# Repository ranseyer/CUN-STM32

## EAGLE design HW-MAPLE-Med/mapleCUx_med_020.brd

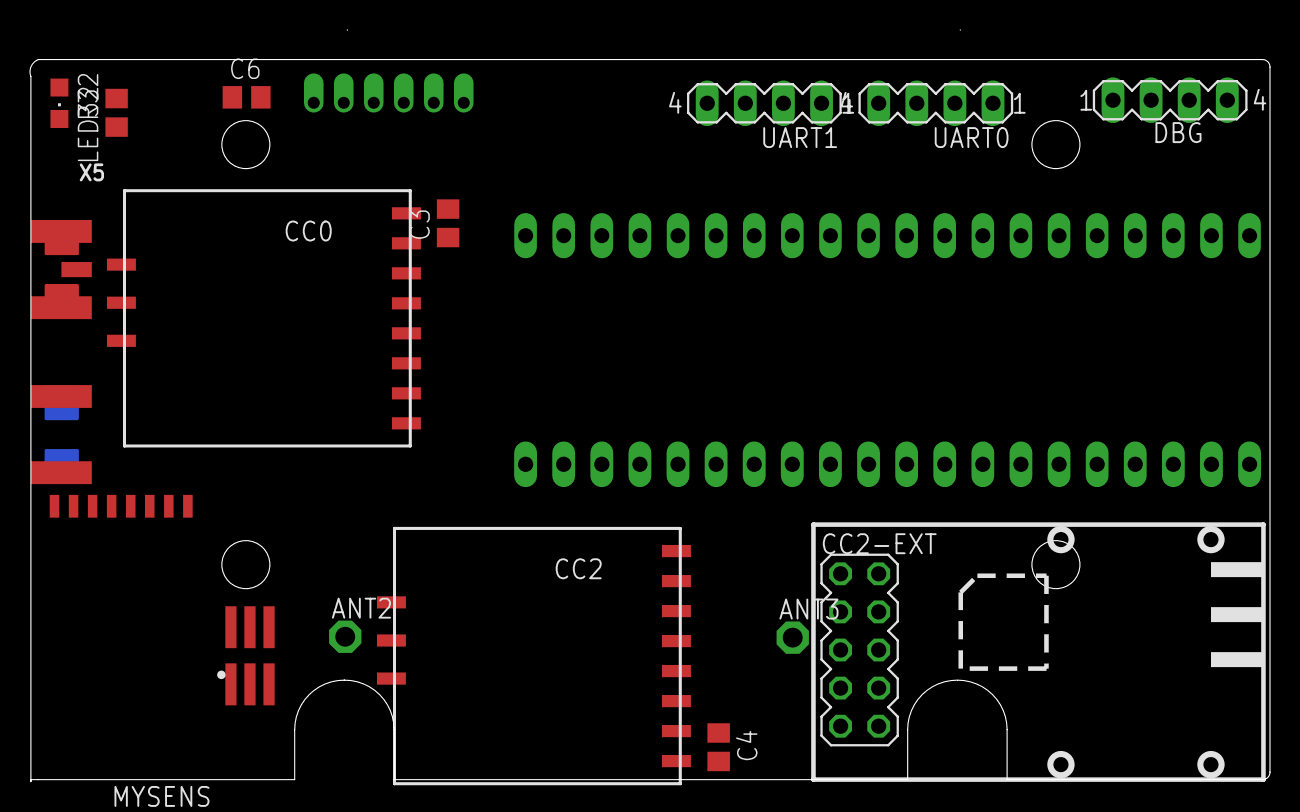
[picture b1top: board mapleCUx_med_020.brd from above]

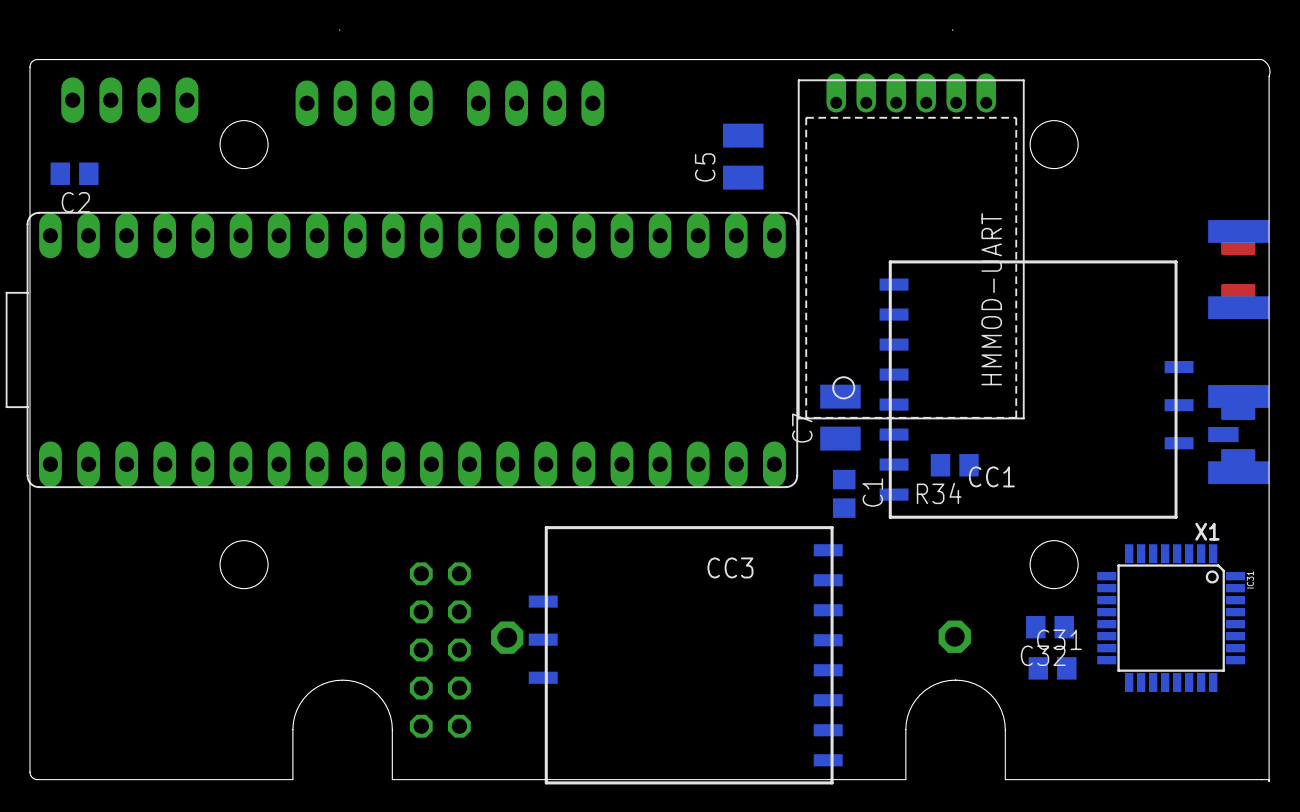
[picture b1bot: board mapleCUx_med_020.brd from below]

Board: 2 copper layers, 82.7 x 50.1 mm, 29 parts (13 on the bottom side), 36 nets, no tracks yet.

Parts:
ANT2, ANT3: TPPAD1-13; P1-13
C1, C2, C3, C4, C6: 22pF; C0805
C5: 10uF; C1210
C7: 4,7uF; C1210
C31, C32: 100n; C0805
CC0: CC1101; CC1101_MODULE1_SMD
CC1, CC2, CC3: CC1101_MODULE1SMD; CC1101_MODULE1_SMD
CC2-EXT: CC1101_MODULE3_DIL
DBG: MA04-1
HMMOD-UART: HM-MOD-UARTDIL; HM-MOD-UART-DIL
IC31: ATMEGA168-TQFP; TQFP32-08
LED32: CHIPLED_0805
MYSENS: NRF24L01+SMD
R32: 1k; R0805
R34: R0805
U$4: MAPLEMINI; 20-DIP
UART0, UART1: MA04-1
X1, X5: SMA_EDGELAUNCH_UFL
X31: M03X2; 2X03-1.27MM_SMD

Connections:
CC_CS0: CC0.CSN, U$4.29
CC_CS1: CC1.CSN, U$4.35
CC_CS2: CC2.CSN, CC2-EXT.CSN, U$4.4
CC_CS3: CC3.CSN, U$4.25
CC_IN_0: CC0.GDO2, U$4.33
CC_IN_1: CC1.GDO2, U$4.7
CC_IN_2: CC2.GDO2, CC2-EXT.GDO2, U$4.5
CC_IN_3: CC3.GDO2, U$4.37
CC_OUT_0: CC0.GDO0, U$4.32
CC_OUT_1: CC1.GDO0, U$4.6
CC_OUT_2: CC2.GDO0, CC2-EXT.GDO0, U$4.36
CE-A: IC31.13, MYSENS.CE
CSN-A: IC31.14, MYSENS.CSN
GND: C1.1, C2.1, C3.1, C4.1, C5.2, C6.2, C7.2, C31.2, C32.2, CC0.GND@0, CC0.GND@1, CC0.GND@2, CC1.GND@0, CC1.GND@1, CC1.GND@2, CC2.GND@0, CC2.GND@1, CC2.GND@2, CC2-EXT.GND@0, CC2-EXT.GND@1, CC3.GND@0, CC3.GND@1, CC3.GND@2, DBG.4, HMMOD-UART.2, IC31.3, IC31.5, IC31.21, LED32.C, MYSENS.GND, U$4.2, U$4.24, U$4.39, UART0.4, UART1.4, X1.GND@1, X1.GND@2, X1.GND@3, X1.GND@4, X5.GND@1, X5.GND@2, X5.GND@3, X5.GND@4, X31.P$6
IRQ-A: IC31.32, MYSENS.IRQ
M-RES: IC31.29, R34.2, X31.P$5
M-SCK: IC31.17, MYSENS.SCK, X31.P$3
MISO1: CC0.MISO, CC1.MISO, CC2.MISO, CC2-EXT.MISO, CC3.MISO, U$4.27
MISO-A: IC31.16, MYSENS.MISO, X31.P$1
MOSI1: CC0.MOSI, CC1.MOSI, CC2.MOSI, CC2-EXT.MOSI, CC3.MOSI, U$4.26
MOSI-A: IC31.15, MYSENS.MOSI, X31.P$4
unnamed: CC1.ANT, X1.P
unnamed: ANT3.TP, CC3.ANT
unnamed: ANT2.TP, CC2.ANT
unnamed: CC0.ANT, X5.P
unnamed: LED32.A, R32.2
unnamed: C32.1, IC31.20
RX1: U$4.22, UART1.3
RX-MAPLE: HMMOD-UART.5, IC31.31, U$4.30, UART0.3
RX_DBG: DBG.3, U$4.14
RX_LED: IC31.2, R32.1
SCK1: CC0.SCLK, CC1.SCLK, CC2.SCLK, CC2-EXT.SCK, CC3.SCLK, U$4.28
TX1: U$4.23, UART1.2
TX-MAPLE: HMMOD-UART.6, IC31.30, U$4.31, UART0.2
TX_DBG: DBG.2, U$4.15
VCC: C1.2, C2.2, C3.2, C4.2, C5.1, C6.1, C7.1, C31.1, CC0.VCC, CC1.VCC, CC2.VCC, CC2-EXT.VCC@0, CC2-EXT.VCC@1, CC3.VCC, DBG.1, HMMOD-UART.1, IC31.4, IC31.6, IC31.18, MYSENS.VCC, R34.1, U$4.1, U$4.40, UART0.1, UART1.1, X31.P$2

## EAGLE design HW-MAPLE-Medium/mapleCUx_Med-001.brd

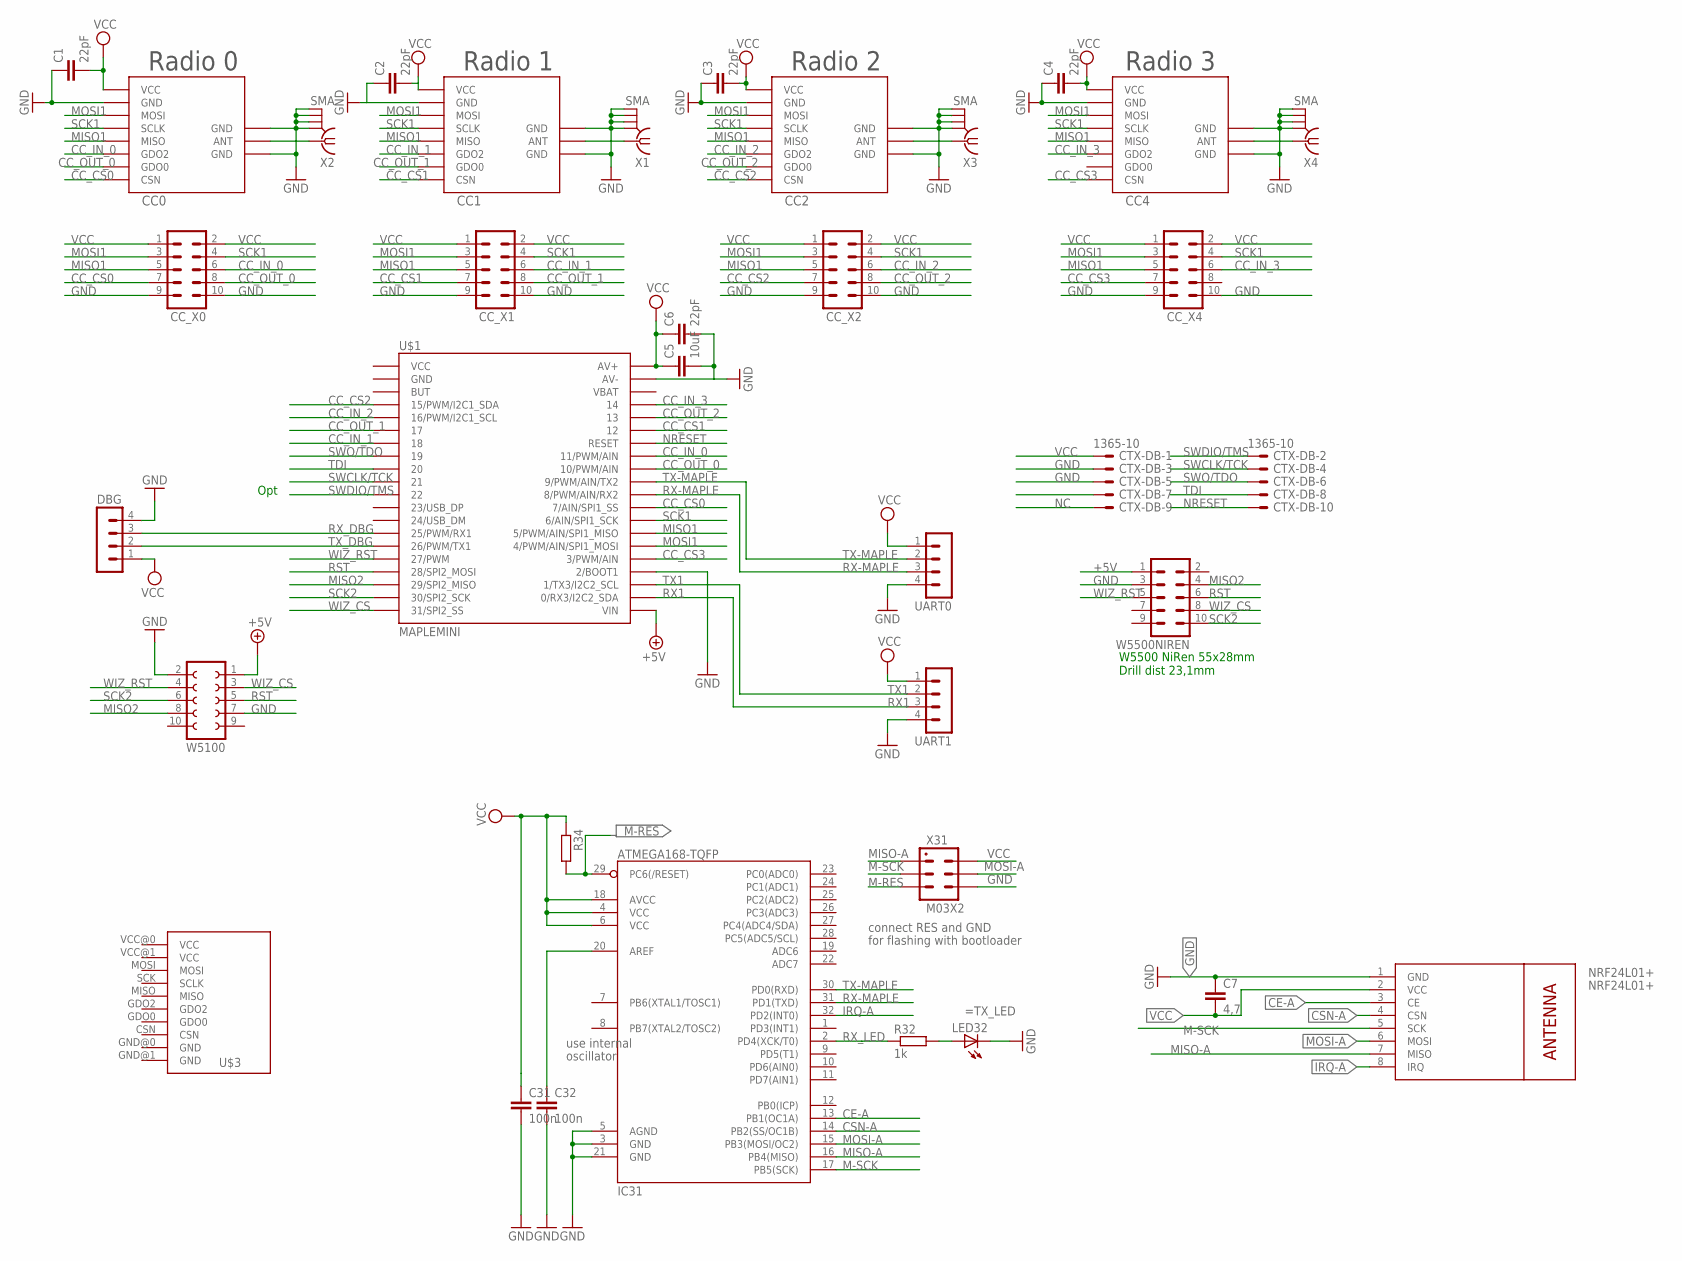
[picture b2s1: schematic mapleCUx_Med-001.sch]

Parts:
C1, C2, C3, C4, C6: 22pF; C0805
C5: 10uF; C1210
C7: 4,7; C1210
C31, C32: 100n; C0805
CC0, CC1, CC2, CC4: CC1101_MODULE1SMD; CC1101_MODULE1_SMD
CC_X0, CC_X1, CC_X2, CC_X4: MA05-2
CTX-DB: 1365-10
DBG: MA04-1
IC31: ATMEGA168-TQFP; TQFP32-08
LED32: LEDCHIPLED_0805; CHIPLED_0805
NRF24L01+: NRF24L01+; WIRELESS-NRF24L01
R32: 1k; R0805
R34: R-EU_R0805; R0805
U$1: MAPLEMINI; 20-DIP
U$3: CC1101_MODULE3_DIL
UART0, UART1: MA04-1
W5100: FE05-2
W5500NIREN: MA05-2
X1, X2, X3, X4: SMA
X31: M03X2; 2X03-1.27MM_SMD

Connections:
+5V: U$1.21 (VIN), W5100.1, W5500NIREN.1
CC_CS0: CC0.CSN, CC_X0.7, U$1.29 (7/AIN/SPI1_SS)
CC_CS1: CC1.CSN, CC_X1.7, U$1.35 (12)
CC_CS2: CC2.CSN, CC_X2.7, U$1.4 (15/PWM/I2C1_SDA)
CC_CS3: CC4.CSN, CC_X4.7, U$1.25 (3/PWM/AIN)
CC_IN_0: CC0.GDO2, CC_X0.6, U$1.33 (11/PWM/AIN)
CC_IN_1: CC1.GDO2, CC_X1.6, U$1.7 (18)
CC_IN_2: CC2.GDO2, CC_X2.6, U$1.5 (16/PWM/I2C1_SCL)
CC_IN_3: CC4.GDO2, CC_X4.6, U$1.37 (14)
CC_OUT_0: CC0.GDO0, CC_X0.8, U$1.32 (10/PWM/AIN)
CC_OUT_1: CC1.GDO0, CC_X1.8, U$1.6 (17)
CC_OUT_2: CC2.GDO0, CC_X2.8, U$1.36 (13)
CE-A: IC31.13 (PB1(OC1A)), NRF24L01+.3 (CE)
CSN-A: IC31.14 (PB2(SS/OC1B)), NRF24L01+.4 (CSN)
GND: C1.1, C2.1, C3.1, C4.1, C5.2, C6.2, C7.1, C31.2, C32.2, CC0.GND@0 (GND), CC0.GND@1 (GND), CC0.GND@2 (GND), CC1.GND@0 (GND), CC1.GND@1 (GND), CC1.GND@2 (GND), CC2.GND@0 (GND), CC2.GND@1 (GND), CC2.GND@2 (GND), CC4.GND@0 (GND), CC4.GND@1 (GND), CC4.GND@2 (GND), CC_X0.9, CC_X0.10, CC_X1.9, CC_X1.10, CC_X2.9, CC_X2.10, CC_X4.9, CC_X4.10, CTX-DB.3, CTX-DB.5, DBG.4, IC31.3 (GND), IC31.5 (AGND), IC31.21 (GND), LED32.C, NRF24L01+.1 (GND), U$1.24 (2/BOOT1), U$1.39 (AV-), U$3.GND@0 (GND), U$3.GND@1 (GND), UART0.4, UART1.4, W5100.2, W5100.7, W5500NIREN.3, X1.GND@1 (2), X1.GND@2 (3), X1.GND@3 (4), X1.GND@4 (5), X2.GND@1 (2), X2.GND@2 (3), X2.GND@3 (4), X2.GND@4 (5), X3.GND@1 (2), X3.GND@2 (3), X3.GND@3 (4), X3.GND@4 (5), X4.GND@1 (2), X4.GND@2 (3), X4.GND@3 (4), X4.GND@4 (5), X31.P$6 (6)
IRQ-A: IC31.32 (PD2(INT0)), NRF24L01+.8 (IRQ)
M-RES: IC31.29 (PC6(/RESET)), R34.2, X31.P$5 (5)
M-SCK: IC31.17 (PB5(SCK)), NRF24L01+.5 (SCK), X31.P$3 (3)
MISO1: CC0.MISO, CC1.MISO, CC2.MISO, CC4.MISO, CC_X0.5, CC_X1.5, CC_X2.5, CC_X4.5, U$1.27 (5/PWM/AIN/SPI1_MISO)
MISO2: U$1.18 (29/SPI2_MISO), W5100.8, W5500NIREN.4
MISO-A: IC31.16 (PB4(MISO)), NRF24L01+.7 (MISO), X31.P$1 (1)
MOSI1: CC0.MOSI, CC1.MOSI, CC2.MOSI, CC4.MOSI, CC_X0.3, CC_X1.3, CC_X2.3, CC_X4.3, U$1.26 (4/PWM/AIN/SPI1_MOSI)
MOSI-A: IC31.15 (PB3(MOSI/OC2)), NRF24L01+.6 (MOSI), X31.P$4 (4)
unnamed: CC2.ANT, X3.1
unnamed: CC4.ANT, X4.1
unnamed: CC1.ANT, X1.1
unnamed: CC0.ANT, X2.1
unnamed: LED32.A, R32.2
unnamed: C32.1, IC31.20 (AREF)
NC: CTX-DB.9
NRESET: CTX-DB.10, U$1.34 (RESET)
RST: U$1.17 (28/SPI2_MOSI), W5100.5, W5500NIREN.6
RX1: U$1.22 (0/RX3/I2C2_SDA), UART1.3
RX-MAPLE: IC31.31 (PD1(TXD)), U$1.30 (8/PWM/AIN/RX2), UART0.3
RX_DBG: DBG.3, U$1.14 (25/PWM/RX1)
RX_LED: IC31.2 (PD4(XCK/T0)), R32.1
SCK1: CC0.SCLK, CC1.SCLK, CC2.SCLK, CC4.SCLK, CC_X0.4, CC_X1.4, CC_X2.4, CC_X4.4, U$1.28 (6/AIN/SPI1_SCK)
SCK2: U$1.19 (30/SPI2_SCK), W5100.6, W5500NIREN.10
SWCLK/TCK: CTX-DB.4, U$1.10 (21)
SWDIO/TMS: CTX-DB.2, U$1.11 (22)
SWO/TDO: CTX-DB.6, U$1.8 (19)
TDI: CTX-DB.8, U$1.9 (20)
TX1: U$1.23 (1/TX3/I2C2_SCL), UART1.2
TX-MAPLE: IC31.30 (PD0(RXD)), U$1.31 (9/PWM/AIN/TX2), UART0.2
TX_DBG: DBG.2, U$1.15 (26/PWM/TX1)
VCC: C1.2, C2.2, C3.2, C4.2, C5.1, C6.1, C7.2, C31.1, CC0.VCC, CC1.VCC, CC2.VCC, CC4.VCC, CC_X0.1, CC_X0.2, CC_X1.1, CC_X1.2, CC_X2.1, CC_X2.2, CC_X4.1, CC_X4.2, CTX-DB.1, DBG.1, IC31.4 (VCC), IC31.6 (VCC), IC31.18 (AVCC), NRF24L01+.2 (VCC), R34.1, U$1.40 (AV+), U$3.VCC@0 (VCC), U$3.VCC@1 (VCC), UART0.1, UART1.1, X31.P$2 (2)
WIZ_CS: U$1.20 (31/SPI2_SS), W5100.3, W5500NIREN.8
WIZ_RST: U$1.16 (27/PWM), W5100.4, W5500NIREN.5

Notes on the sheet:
Radio 1
Radio 0
Opt
Radio 2
Radio 3
W5500 NiRen 55x28mm Drill dist 23,1mm
use internal
oscillator
=TX_LED
connect RES and GND
for flashing with bootloader

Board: 2 copper layers, 35 parts (0 on the bottom side), 47 nets, no tracks yet.

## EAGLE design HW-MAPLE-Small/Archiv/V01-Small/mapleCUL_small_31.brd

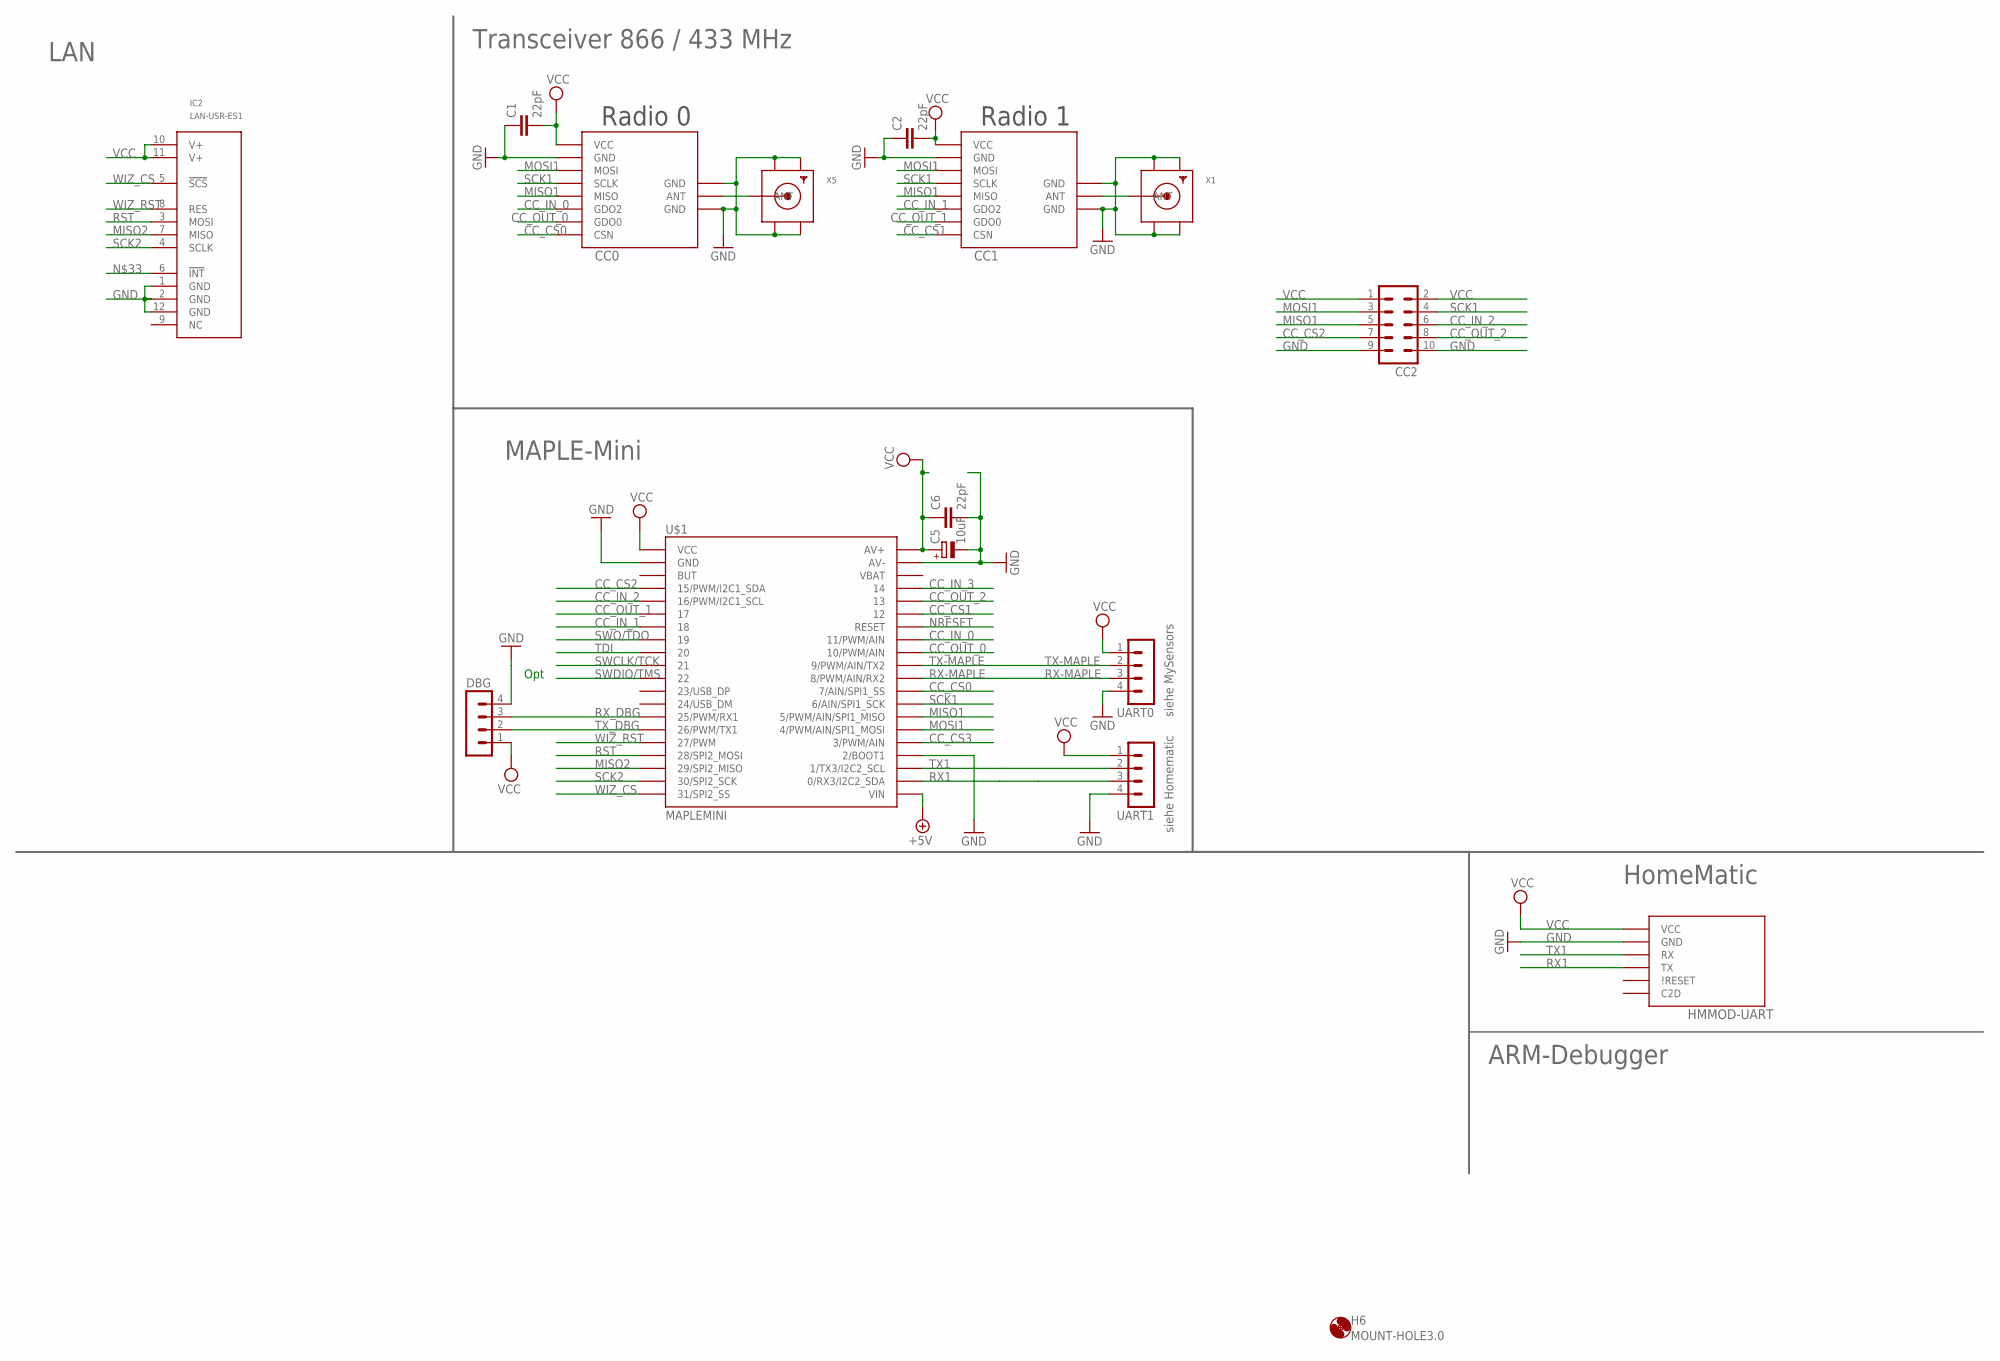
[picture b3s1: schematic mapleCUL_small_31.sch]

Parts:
C1, C2, C6: 22pF; C0805
C5: 10uF; R/2012-12W
CC0: CC1101; CC1101_MODULE1_SMD
CC1: CC1101_MODULE1SMD; CC1101_MODULE1_SMD
CC2: MA05-2
DBG: MA04-1
H6: MOUNT-HOLE3.0; 3,0
HMMOD-UART: HM-MOD-UARTDIL; HM-MOD-UART-DIL
IC2: LAN-USR-ES1; USR-ES1
U$1: MAPLEMINI; 20-DIP
UART0, UART1: MA04-1
X1, X5: SMACONNECTOR_EDGE_UFL; SMA_EDGELAUNCH_UFL

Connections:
+5V: U$1.21 (VIN)
CC_CS0: CC0.CSN, U$1.29 (7/AIN/SPI1_SS)
CC_CS1: CC1.CSN, U$1.35 (12)
CC_CS2: CC2.7, U$1.4 (15/PWM/I2C1_SDA)
CC_CS3: U$1.25 (3/PWM/AIN)
CC_IN_0: CC0.GDO2, U$1.33 (11/PWM/AIN)
CC_IN_1: CC1.GDO2, U$1.7 (18)
CC_IN_2: CC2.6, U$1.5 (16/PWM/I2C1_SCL)
CC_IN_3: U$1.37 (14)
CC_OUT_0: CC0.GDO0, U$1.32 (10/PWM/AIN)
CC_OUT_1: CC1.GDO0, U$1.6 (17)
CC_OUT_2: CC2.8, U$1.36 (13)
GND: C1.1, C2.1, C5.-, C6.2, CC0.GND@0 (GND), CC0.GND@1 (GND), CC0.GND@2 (GND), CC1.GND@0 (GND), CC1.GND@1 (GND), CC1.GND@2 (GND), CC2.9, CC2.10, DBG.4, HMMOD-UART.2 (GND), IC2.1 (GND), IC2.2 (GND), IC2.12 (GND), U$1.2 (GND), U$1.24 (2/BOOT1), U$1.39 (AV-), UART0.4, UART1.4, X1.GND@1 (GND1), X1.GND@2 (GND2), X1.GND@3 (GND3), X1.GND@4 (GND4), X5.GND@1 (GND1), X5.GND@2 (GND2), X5.GND@3 (GND3), X5.GND@4 (GND4)
MISO1: CC0.MISO, CC1.MISO, CC2.5, U$1.27 (5/PWM/AIN/SPI1_MISO)
MISO2: IC2.7 (MISO), U$1.18 (29/SPI2_MISO)
MOSI1: CC0.MOSI, CC1.MOSI, CC2.3, U$1.26 (4/PWM/AIN/SPI1_MOSI)
unnamed: CC1.ANT, X1.P (ANT)
unnamed: CC0.ANT, X5.P (ANT)
NRESET: U$1.34 (RESET)
RST: IC2.3 (MOSI), U$1.17 (28/SPI2_MOSI)
RX1: HMMOD-UART.5 (TX), U$1.22 (0/RX3/I2C2_SDA), UART1.3
RX-MAPLE: U$1.30 (8/PWM/AIN/RX2), UART0.3
RX_DBG: DBG.3, U$1.14 (25/PWM/RX1)
SCK1: CC0.SCLK, CC1.SCLK, CC2.4, U$1.28 (6/AIN/SPI1_SCK)
SCK2: IC2.4 (SCLK), U$1.19 (30/SPI2_SCK)
SWCLK/TCK: U$1.10 (21)
SWDIO/TMS: U$1.11 (22)
SWO/TDO: U$1.8 (19)
TDI: U$1.9 (20)
TX1: HMMOD-UART.6 (RX), U$1.23 (1/TX3/I2C2_SCL), UART1.2
TX-MAPLE: U$1.31 (9/PWM/AIN/TX2), UART0.2
TX_DBG: DBG.2, U$1.15 (26/PWM/TX1)
VCC: C1.2, C2.2, C5.+, C6.1, CC0.VCC, CC1.VCC, CC2.1, CC2.2, DBG.1, HMMOD-UART.1 (VCC), IC2.10 (V+), IC2.11 (V+), U$1.1 (VCC), U$1.40 (AV+), UART0.1, UART1.1
WIZ_CS: IC2.5 (!SCS!), U$1.20 (31/SPI2_SS)
WIZ_RST: IC2.8 (RES), U$1.16 (27/PWM)

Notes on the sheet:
Radio 1
Radio 0
Opt
siehe Homematic
siehe MySensors
HomeMatic
MAPLE-Mini
Transceiver 866 / 433 MHz
LAN
ARM-Debugger

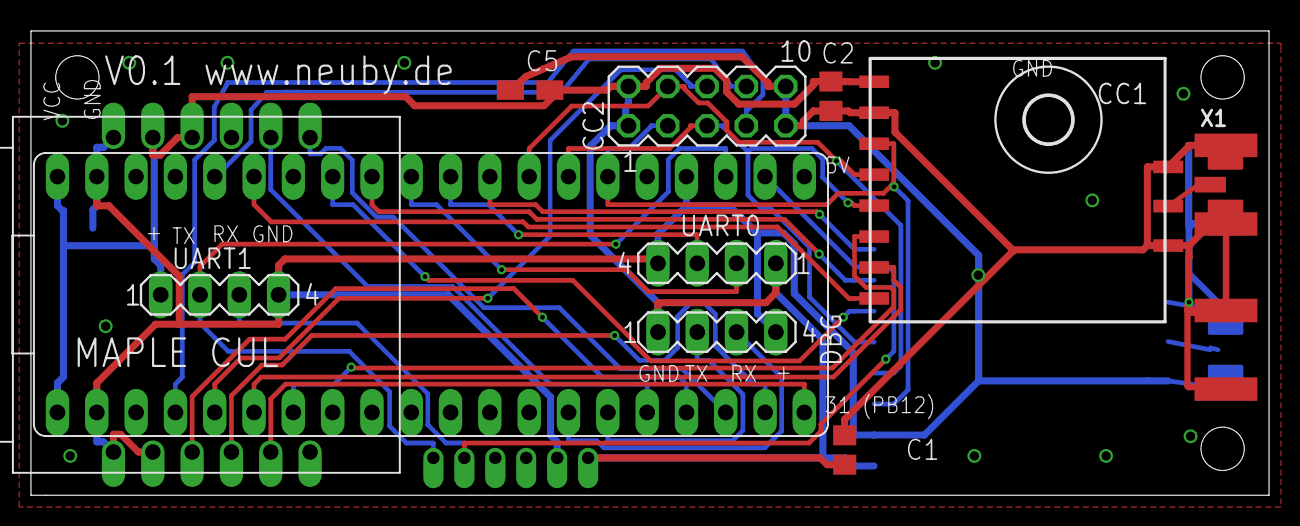
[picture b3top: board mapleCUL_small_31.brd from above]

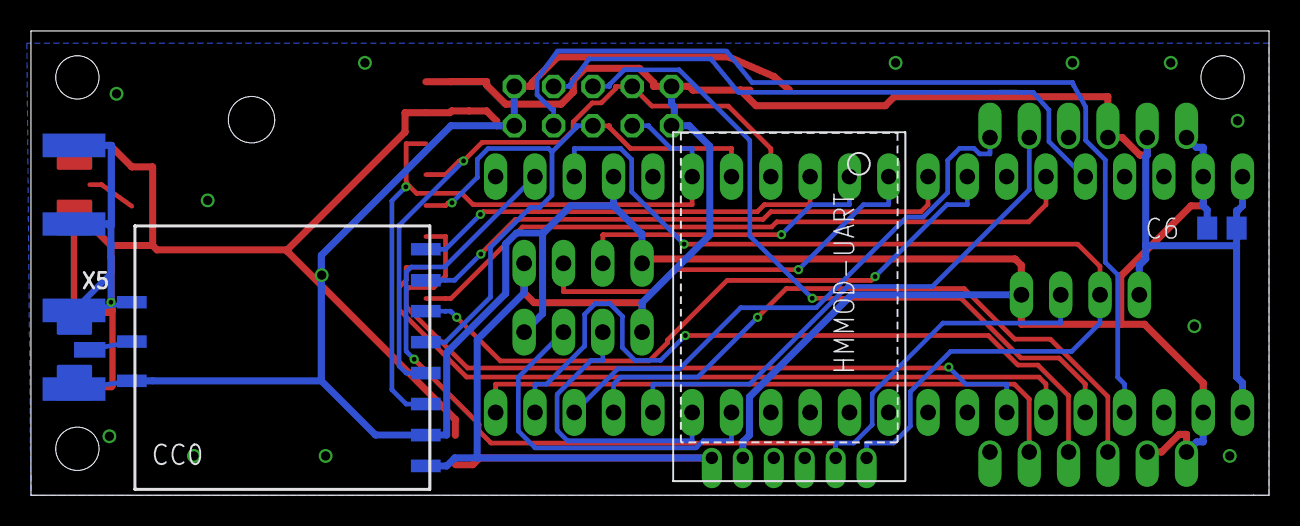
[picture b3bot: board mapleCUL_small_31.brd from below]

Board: 2 copper layers, 80.0 x 30.0 mm, 16 parts (4 on the bottom side), 27 nets.

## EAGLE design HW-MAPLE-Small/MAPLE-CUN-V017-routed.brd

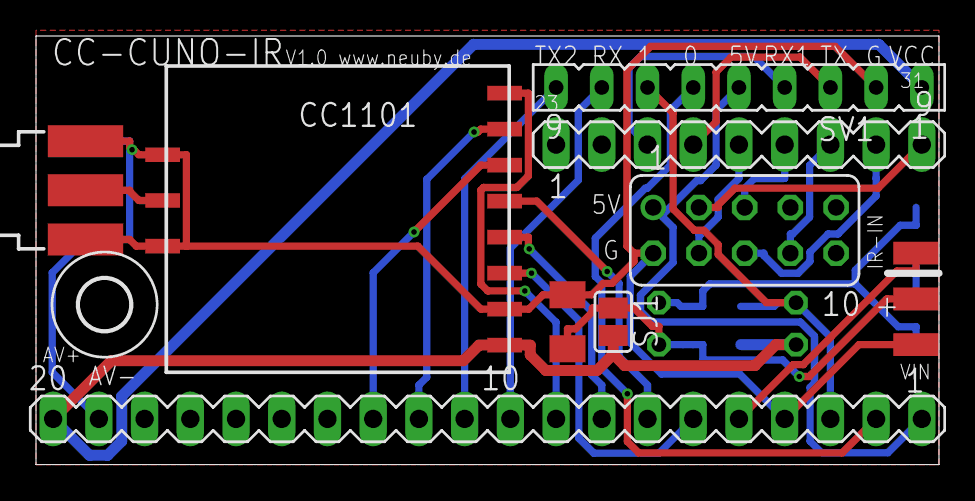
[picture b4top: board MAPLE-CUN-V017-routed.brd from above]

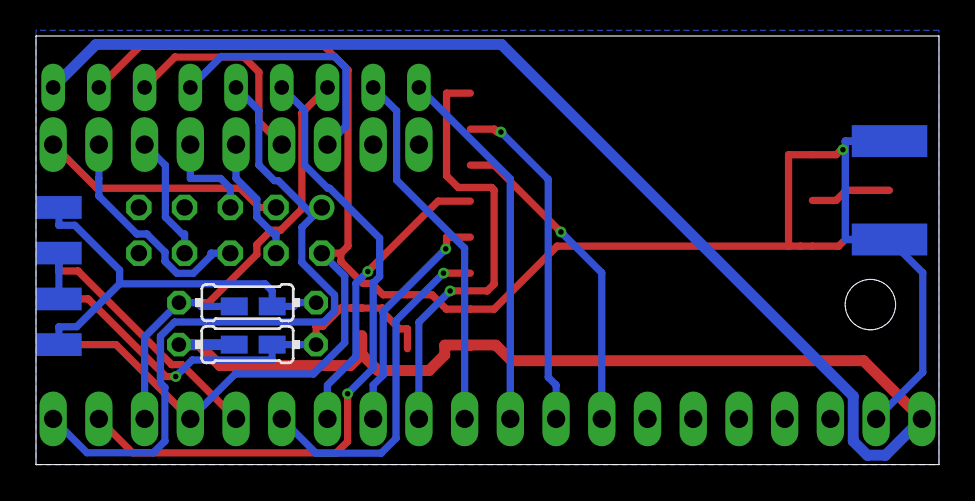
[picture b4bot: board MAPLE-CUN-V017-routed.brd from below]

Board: 2 copper layers, 50.2 x 23.8 mm, 20 parts (8 on the bottom side), 25 nets.

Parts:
C2: 4,7uF; C1206K
CC1101: CC1101_MODULE1SMD; CC1101_MODULE1_SMD
GND: SMD1,27-2,54
H1: MOUNT-HOLE2.8; 2,8
IR+: SMD1,27-2,54
IR-IN: SMD1,27-2,54
PC+: SMD1,27-2,54
PC-: SMD1,27-2,54
PWR+: SMD1,27-2,54
PWR-: SMD1,27-2,54
R2: 100; 0204/7
R3: 100; R0805W
R5: 220; 0204/7
R7: 220; R0805W
SJ1: SJ
SV1: FE09
SV4: MA20-1
SV5: MA09-1
W5100: FE05-2
X1: SMA

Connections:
0-PB11: SV1.6, SV4.2
1-PB10: R5.1, R7.1, SV1.7, SV4.3
3-PB0: IR-IN.1, SV4.5
+5V: SV1.5, SV4.1, W5100.1
CC_IN_0: CC1101.GDO2, SV4.13
CC_OUT_0: CC1101.GDO0, SV4.12
CSN: CC1101.CSN, SV4.9
GND: C2.2, CC1101.GND@0, CC1101.GND@1, CC1101.GND@2, GND.1, SV1.2, SV4.4, SV4.19, W5100.2, X1.GND@1, X1.GND@2, X1.GND@3, X1.GND@4
IR+: C2.1, IR+.1, R2.1, R3.1, SJ1.1
MISO2: SV5.7, W5100.8
MOSI: CC1101.MOSI, SV4.6
MOSI2: SV5.6, W5100.5
unnamed: CC1101.ANT, X1.1
unnamed: CC1101.MISO, SV4.7
unnamed: CC1101.SCLK, SV4.8
PWR+: PC+.1, PWR+.1, R5.2, R7.2
PWR-: PC-.1, PWR-.1
RX1: SV1.4, SV5.3
S2RX: SV1.8, SV4.10
S2TX: SV1.9, SV4.11
SCK2: SV5.8, W5100.6
TX1: SV1.3, SV5.4
VCC: CC1101.VCC, R2.2, R3.2, SJ1.2, SV1.1, SV4.20
WIZ_CS: SV5.9, W5100.3
WIZ_RST: SV5.5, W5100.4

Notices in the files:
parts and their libraries:
diy-modules: Released under the Creative Commons Attribution 4.0 International License: http://creativecommons.org/licenses/by/4.0
